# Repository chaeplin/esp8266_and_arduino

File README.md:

* ESP8266 mqtt node

#### Server ####
- mqtt broker : mosquitto
- db : influxdb
- web : grafana, node-red
- collect : mqtt2graphite
- alert : mqttwarn
- control : slack + rtmbot
- define MQTT_MAX_PACKET_SIZE 350

### IDE ###
- CURRENT : Arduino 1.6.8 with git version of https://github.com/esp8266/Arduino

### Library ###
- https://github.com/knolleary/pubsubclient
- https://github.com/milesburton/Arduino-Temperature-Control-Library
- https://github.com/chaeplin/PietteTech_DHT-8266
- https://github.com/bogde/HX711
- https://github.com/Makuna/Rtc
- LiquidCrystal_I2C.h
- https://github.com/openenergymonitor/EmonLib
- https://github.com/bblanchon/ArduinoJson
- https://github.com/MajenkoLibraries/Average
- https://github.com/Yveaux/arduino_vcc
- https://github.com/PaulStoffregen/Time
- https://github.com/z3t0/Arduino-IRremote
- https://github.com/JChristensen/Timer

| name | esp | arduino | desc |
|------|-----|---------|------|
| _01-door-alarm | esp-12 | pro mini | alarm door status using mqtt. first one to learn esp, didn't know how to wake up esp using external intterupt. replaced with _06-power_meter. check _15-esp8266-dash-deepsleep-reset and _48-door-alarm-deepsleep for latest | 
| _02-mqtt-sw-temperature | esp-12 | | control lamp, pub temp, pub radio data. nrf24l01P |
| _03-hx711-scale | esp-12 | pro mini | pub measured weight of pet. hx711, 4 * body scale load cell |
| _04-lcd-dust | esp-01 | nano | display mqtt msg, pub temp/hum, dust, control ir |
| _05-two-ds18b20 | esp-12 | | pub temp. ds18b20. to check deepsleep and life of 2 * AA battery |
| _06-power_meter | esp-12 | | pub power usage, door status. using CT sensor and ADC ---> replaced by _49-emontxv2-esp-01-i2c|
| _07-ac-ir-remote-timer | | pro mini | |
| _08_hc-sr04 | | | hc-sr04 test |
| _09_ir_tx_rx | | nano | to control tv using ir |
| _10-syslog | esp | | udp/syslog example |
| _11-mqtt-lwt-test | esp | | mqtt lwy test |
| _12-wifiscan | esp | | wifi scan test |
| _13-mfrc522-esp8266 | esp | | rfid mfrc522 test |
| _14-mqtt-reconnect-with-reset | esp | | |
| _15-esp8266-dash-deepsleep-reset | esp | | to coltrol lamp. dash like button |
| _16-mqtt-pub-100ms-50ms | esp | | pub test |
| _17-two-esp-one-pub-50ms-one-sub-pub-50ms | esp | | pub test |
| _18-adc-test-using-sdk-1.5| esp | | adc test |
| _19-wifi-test-using-sdk-1.5| esp | | wifi test |
| _20-esp8266-dash-deepsleep-test | esp | | test of _15-esp8266-dash-deepsleep-reset |
| _21-sntp | esp | | sntp test |
| _22-CheckFlashConfig | esp | | CheckFlashConfig |
| _23-attiny85-ir | | tiny85 | ir tx test |
| _24-attiny85-wdt-sleep | | tiny85 | sleep test |
| _25-attiny85-nrf24-ds18b20 | | tiny85 | temp sensor |
| _26-attiny85-nrf24-pin-change-int | | tiny85 | pc int test |
| _27-attiny85-two-85-boost | | tiny85 | distance test |
| _28-attiny85-nrf24-3pin-ir | | tiny85 | distance using ir. checking toilet paper roll |
| _29-attiny85-nrf24-5pin-pin-change-int | | tiny85 | check door bell |
| _30-attiny85-nrf24-5pin-pin-change-int | | tiny85 | check door bell. last one |
| _31-esp-12-gps-ntpd | esp | | gps + ntpd test |
| _32-esp-12-BasicOTA | esp | | ota test |
| _33-esp-12-WiFiClientSecure-mqtt-ssl | esp | | mqtt tlsv1.1 with ip |
| _34-esp-12-WiFiClientSecure-mqtt-ssl-using-dns | esp | | mqtt tlsv1.1 with name |
| _35-esp-12-wpa2-enterprise | esp | | wpa2-enterprise  |
| _36-esp-rtc-mem-test | esp | | rtc mem test |
| _37-wifi-off-modem-sleep | esp | | modem off test |
| _38-wifi-off-light-sleep | esp | | light sleep test |
| _39_esp12-random-test | esp | | random number gen |
| _40_esp12-random-test-udp-report | esp | | random number gen |
| _41-promini-nrf24-ads1115 | | pro mini | i2c adc ads1115 |
| _42-promini-nrf24-32byte | | pro mini | nrf24 32byte test|
| _43-PietteTech_DHT-8266 | esp | | interrup driven dht22 test |
| _44-esp-atmega328p-spi | esp | atmega328p | spi multi byte test |
| _45-esp-atmega328p-i2c | esp | atmega328p | i2c multi byte test |
| _46-esp-atmega328p-spi-i2c | esp | atmega328p | spi and i2c multi byte test |
| _47-esp-dht22-2AA-deepsleep-test | esp | | dht22 test |
| _48-door-alarm-deepsleep | esp | | | door alarm using reed switch |
| _49-emontxv2-esp-01-i2c | esp-01 | atmega328p | emontx v2 plus esp-01 and ds1307. test | 
| _50-promini-nrf24-getntp | | pro mini | nrf24 ntp test |
| _51-attiny85-nrf24-lcd-getntp | | tiny85 | tiny85 spi and i2c mixing |
| _52-attiny85-hx711-nrf24-deprecated | | tiny85 | nrf24 / hx711 / gy-521 test, flash is small |
| _53-esp-01-i2c-lcd | esp-01 | | i2c lcd test |
| _54-atmega328p-nrf24-gy-521-hx711 | | atmega328p | second version of sacle for pet |
| _55-tiny85-dtr-control-esp8266 | | tiny85 | auto reset on Xbee programmer |
| _56-gopro-control | esp-01 | | 4M flash version, to upload gopro picture to twitter |
| _57-tiny85-cds-pir | | tiny85 | to turn off light which has touch sensor |
| _58-esp8266-tyny85-dash-button | esp-01 | tiny85 | second version of dash button |
| _59-esp8266-tyny85-i2c8x8-dash-button | esp-01 | tiny85 | 3rd version of dash button |
| _60-tiny85-pin-int | |tiny85 | PinChangeInterrupt lib test |
| _61-mma-8452-promini | | pro mini | mma-8452 test | 

#### _02-mqtt-sw ####
- esp-12 + nrf24l01p
- power(5v + 3.3V), fuse(10A + 73°C thermal), 1CH relay, SW(top + lamp), PIR, DS18B20(out)
- on/off lamp using mqtt, pub temp outside/pir

#### _03-hx711-scale ####
- esp-12 +(i2c) pro mini
- hx711, load cell, tilt sw
- pub measured weight of pet

#### _04-mqtt-lcd-dust-sensor ####
- esp-01 +(i2c) nano
- lcd(i2c), rtc(i2c), level convertor, Sharp dust sensor, IR sned/recv, dht22
- display clock, temp/humidity(mqtt sub), dust
- control LG_AC using Apple remote

#### _06-power-meter ####
- esp-12
- CT sensor, line tracker
- pub power usage

### _15-esp8266-dash-deepsleep-reset ###
- esp-12
- dash like button
- to control lamp sw

#### _29-attiny85-nrf24-5pin-pin-change-int / _30-attiny85-nrf24-5pin-pin-change-int ####
- attiny 85 + nrf24l01p
- optical isolator
- for door bell
- _30-attiny85-nrf24-5pin-pin-change-int is last one using gammon's wdt

#### _25-attiny85-nrf24-ds18b20 ####
- attiny 85 + nrf24l01p
- two ds18b20
- to check temp

#### _28-attiny85-nrf24-3pin-ir ####
- attiny 85 + nrf24l01p
- ir send and receiver
- to check roll

#### _41-promini-nrf24-ads1115 ###
- pro mini(3.3V) + nrf24l01p + µCurrent GOLD
- to report current measure

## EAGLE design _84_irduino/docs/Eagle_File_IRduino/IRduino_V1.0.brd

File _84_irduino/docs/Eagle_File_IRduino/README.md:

# Eagle_File_IRduino
Eagle file for IRduino

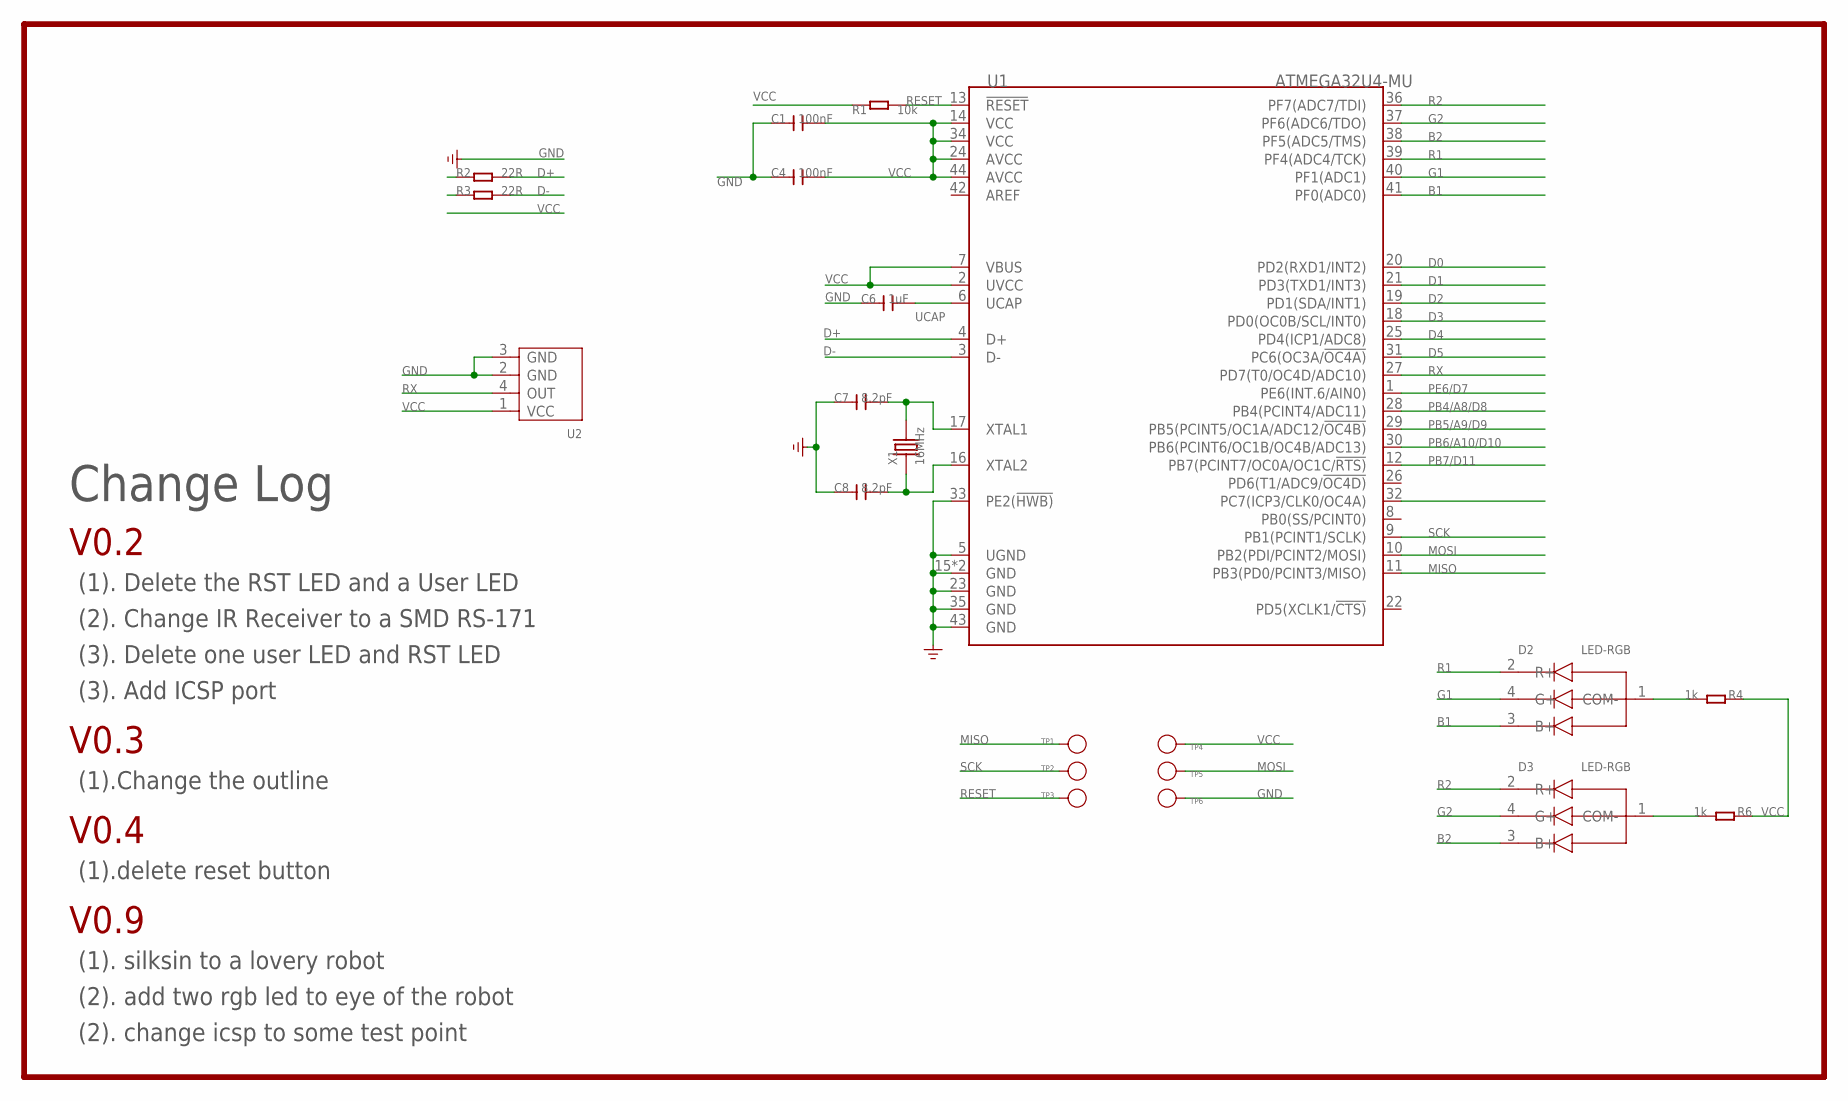
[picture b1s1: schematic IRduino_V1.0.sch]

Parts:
C1, C4: 100nF; C0603
C6: 1uF; C0603
C7, C8: 8.2pF; C0603
D2, D3: LED-RGB; 4P-SMD-1.6X1.5
R1: 10k; R0603
R2, R3: 22R; R0603
R4, R6: 1k; R0603
TP1, TP2, TP3, TP4, TP5, TP6: PAD-TEST-POINT'3535'; TP_3535
U1: ATMEGA32U4-MU; QFN44
U2: RS-171; 4P-SMD-L7.6*W5.75MM
X1: 16MHz; 2P-SMD-5X3.2

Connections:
B1: D2.3 (B+), U1.41 (PF0(ADC0))
B2: D3.3 (B+), U1.38 (PF5(ADC5/TMS))
D0: U1.20 (PD2(RXD1/INT2))
D1: U1.21 (PD3(TXD1/INT3))
D2: U1.19 (PD1(SDA/INT1))
D3: U1.18 (PD0(OC0B/SCL/INT0))
D4: U1.25 (PD4(ICP1/ADC8))
D5: U1.31 (PC6(OC3A/!OC4A))
D+: R2.2, U1.4 (D+)
D++: R2.1
D-: R3.2, U1.3 (D-)
D--: R3.1
G1: D2.4 (G+), U1.40 (PF1(ADC1))
G2: D3.4 (G+), U1.37 (PF6(ADC6/TDO))
GND: C1.1, C4.1, C6.1, C7.1, C8.1, TP6.T, U1.5 (UGND), U1.15 (GND), U1.23 (GND), U1.33 (PE2(!HWB)), U1.35 (GND), U1.43 (GND), U1.TAB (GND), U2.2 (GND), U2.3 (GND)
MISO: TP1.T, U1.11 (PB3(PD0/PCINT3/MISO))
MOSI: TP5.T, U1.10 (PB2(PDI/PCINT2/MOSI))
unnamed: D2.1 (COM-), R4.2
unnamed: D3.1 (COM-), R6.2
unnamed: C7.2, U1.17 (XTAL1), X1.2
unnamed: C8.2, U1.16 (XTAL2), X1.1
PB4/A8/D8: U1.28 (PB4(PCINT4/ADC11))
PB5/A9/D9: U1.29 (PB5(PCINT5/OC1A/ADC12/!OC4B))
PB6/A10/D10: U1.30 (PB6(PCINT6/OC1B/OC4B/ADC13))
PB7/D11: U1.12 (PB7(PCINT7/OC0A/OC1C/!RTS))
PE6/D7: U1.1 (PE6(INT.6/AIN0))
R1: D2.2 (R+), U1.39 (PF4(ADC4/TCK))
R2: D3.2 (R+), U1.36 (PF7(ADC7/TDI))
RESET: R1.2, TP3.T, U1.13 (!RESET)
RX: U1.27 (PD7(T0/OC4D/ADC10)), U2.4 (OUT)
SCK: TP2.T, U1.9 (PB1(PCINT1/SCLK))
UCAP: C6.2, U1.6 (UCAP)
VCC: C1.2, C4.2, R1.1, R4.1, R6.1, TP4.T, U1.2 (UVCC), U1.7 (VBUS), U1.14 (VCC), U1.24 (AVCC), U1.34 (VCC), U1.44 (AVCC), U2.1 (VCC)

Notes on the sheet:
Change Log
(1). Delete the RST LED and a User LED
(2). Change IR Receiver to a SMD RS-171
(3). Delete one user LED and RST LED
V0.2
V0.3
(3). Add ICSP port
(1).Change the outline
V0.4
(1).delete reset button
V0.9
(1). silksin to a lovery robot
(2). add two rgb led to eye of the robot
(2). change icsp to some test point

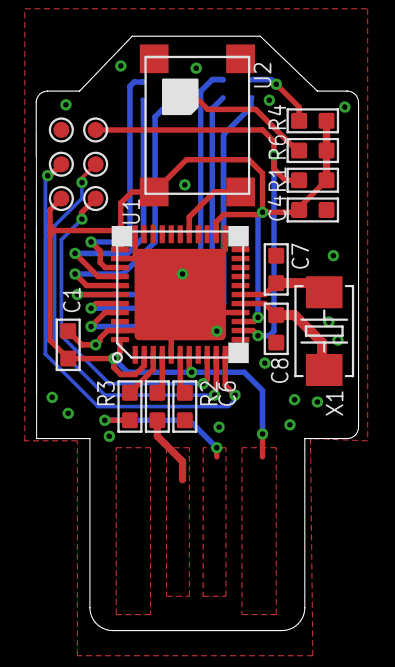
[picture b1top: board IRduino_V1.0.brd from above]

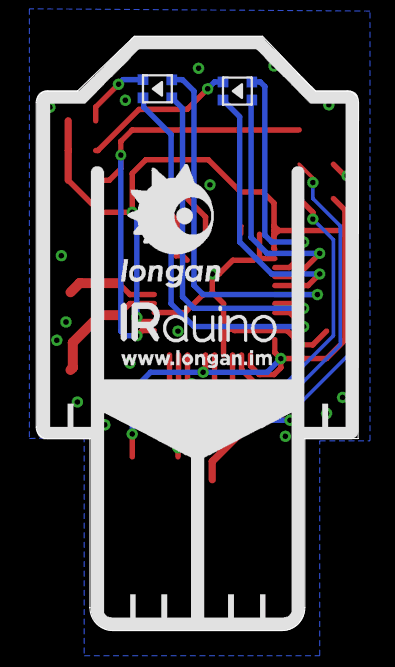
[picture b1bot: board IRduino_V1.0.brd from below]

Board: 2 copper layers, 17.9 x 33.0 mm, 21 parts (2 on the bottom side), 20 nets.

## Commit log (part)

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2016-01-10 calibration
2016-01-10 calibrated
2016-01-10 two ds18b20
2016-01-12 wifi from 1.54 sec to 210ms
2016-01-13 to find cause of reset
2016-01-16 changing cpu to 160MHz over OTA
    no more reset(2day now)
2016-01-17 checking pulse counter of power
2016-01-18 verify fingerprint using host name
2016-01-18 certificate verify
2016-01-19 WPA2-ENTERPRISE
2016-01-20 FreeHeap
2016-01-21 remove noise in pulse counting
2016-01-21 rf24 to rf24 PA/LNA version
2016-01-21 ap_setting.h change, pic add
2016-01-21 reduce wifi connect time to 150 ~ 220ms
2016-01-21 wifi 1.1sec to 152ms
2016-01-23 adjusting report, crt for mqtt client
2016-01-23 remove mqtt cert
2016-01-23 Revert "remove mqtt cert"
    This reverts commit b0061a696f73f3985e871476636015dbbec1f3fe.
2016-01-23 Revert "Revert "remove mqtt cert""
    This reverts commit 7b608709c7d80b3ee336f10499d51f25ff61dc48.
2016-01-25 static ip
2016-01-26 MODEM_SLEEP
2016-01-26 wifi_fpm_set_wakeup_cb : not work
2016-01-28 tx power and rate limit
2016-01-28 msg to influxdb udp
2016-01-28 logging to multiple server
2016-01-29 ads1115 test
2016-01-29 delay change
2016-01-30 attachInterrupt and udp test
2016-01-30 PinChangeInterrupt
2016-01-30 add radio channel and sendUdpmsg
2016-01-30 remove PinChangeInterrupt
2016-01-30 nrf24 multi ch and current test
2016-01-30 move radio power up/down
2016-01-30 250 reports / sec
2016-01-31 simple logic / 300 recore / sec
2016-01-31 // for PubSubClient 2.5 #define MQTT_MAX_PACKET_SIZE 250 //#define MQTT_KEEPALIVE 60
2016-01-31 Revert "// for PubSubClient 2.5 #define MQTT_MAX_PACKET_SIZE 250 //#define MQTT_KEEPALIVE 60"
    This reverts commit 972c98eee3b66ee306079ec87a9a2a6522ddc7a8.
2016-01-31 using rtc mem to preserve rev count
2016-02-01 to debug more
2016-02-02 unit to nA
2016-02-02 report light status when booting
2016-02-02 report interval 1 min to 1 sec
2016-02-02 RF24_PA_LOW to RF24_PA_MIN
2016-02-03 1 sec to 10 sec
2016-02-03 radio.enableDynamicPayloads test
2016-02-04 update ampere meter
2016-02-04 radio change
    radio.enableDynamicPayloads,
    radio.setDataRate(RF24_1MBPS),
    radio.setRetries(5, 15),
    break to return,
    preserve light status after reset/update
2016-02-05 data size
2016-02-05 radio.setDataRate(RF24_1MBPS), radio.enableDynamicPayloads
2016-02-09 test PietteTech_DHT
2016-02-09 test
2016-02-09 test 2
2016-02-09 test 3
2016-02-09 radio_test_result
    with setWaitForConversion and PietteTech_DHT-8266
    —> check bool RF24::write
2016-02-10 PietteTech_DHT test
2016-02-10 DHT.acquireAndWait(0)
2016-02-10 _edges debug
2016-02-10 dht edges report
2016-02-10 PietteTech_DHT-8266 timing test with DHT_DEBUG_TIMING on/off
2016-02-11 DHT_DEBUG_TIMING off
2016-02-11 timing
2016-02-11 DHT_DEBUG_TIMING
2016-02-11 DHTLIB_ONE_TIMING
    108 to 109
2016-02-11 DHTLIB_ONE_TIMING, calcIrms, button,
2016-02-12 DHT.getStatus, power meter
2016-02-12 DHT_SAMPLE_INTERVAL
2016-02-13 _sensor_report_count
2016-02-13 remoce locked up and reset of lcd
2016-02-13 swap flash from 512K to 4M
    ./esptool.py -p /dev/cu.usbserial-A703X38A erase_flash
    ./esptool -vv -cd ck -cb 115200 -cp /dev/cu.usbserial-A703X38A -ca
    0x3FC000 -cf ./esp_init_data_default1.5.2.bin
2016-02-13 json update
2016-02-14 lcd update
2016-02-14 ADS1115 + µCurrent GOLD, DHT timeout
2016-02-15 report Cpu Freq
2016-02-15 move up radio
2016-02-17 radio temp, lcd dust, swtemp
    1) swtemp : remove dht22(too many err with this unit, move to lcd dust)
    2) lcd dust : change temp subs topic
    3) radio temp : 10 sec to 60 sec
2016-02-17 add DHT22
2016-02-17 sw-temp : rf24 with irq
2016-02-17 syslog update
2016-02-17 DEBUG_PRINT and RTC
2016-02-17 readme
    rtc add, dht22 moved
2016-02-18 lcd.init
2016-02-18 report 3s to 5s, radio rx option
2016-02-19 debug on
2016-02-19 rtc test is done
    remove rtc
2016-02-19 dust : rtc test again, sw-temp : to 160MHz
2016-02-20 ICACHE_RAM_ATTR test
2016-02-24 nrf24 : with irq : 280, no irq 380
2016-02-26 dht22 110 to 104
2016-02-26 spi test
2016-02-27 i2c test
2016-02-27 i2c twi_setClock
2016-02-27 dht 104 to 110
2016-02-28 Read me
2016-02-28 add source
2016-02-28 i2c result
2016-02-29 move folder
2016-02-29 spi-i2c-test
2016-03-01 drop irq with nrf24l01, add dht22 again
2016-03-01 ds18b20 is nan
2016-03-02 display update
2016-03-03 pin definition
2016-03-03 dht22 deepsleep test
2016-03-04 dht2 remove and deepsleep test
2016-03-05 pic link update
2016-03-05 reset to restart
2016-03-06 button and lcd update
    - button : read me
    - lcd : host count
2016-03-07 blog for button
2016-03-08 lcd, light sleep, dht22
    lcd : report to 5 sec
    light sleep : wake up with gpio event
    dht22 : ladyada’s version test
2016-03-08 light_sleep_current
2016-03-08 scale, light sleep, dht22
    scale : add icmp test
    light sleep : time test
    dht22 : more test
2016-03-09 scale, dht
    scale : icmp
    dht : deepsleep test
2016-03-10 hx711, lcd, button, dht
    hx711 : core to 2.1.0
    lcd /nano : rgb test
    button : more oneshot circuit
    dht : sampling interval
2016-03-12 door alarm
2016-03-12 debug using udp
2016-03-12 current
2016-03-13 power control with GPIO 0
2016-03-14 more test on dht22
2016-03-14 pins
2016-03-14 test : i2c to ds1307, put low SDA
2016-03-16 emontxv2 and hx711
    hx711 : remove detachInterrupt
    emontxv2 : i2c test setup
2016-03-16 esp-01 test setup
2016-03-16 pics
2016-03-16 use interrupt between masters
2016-03-16 add 4.7k pullup to D6 to TX
2016-03-17 adding ct, pulse, and door
2016-03-17 current only test
2016-03-18 for calibration
2016-03-18 add door alarm
2016-03-18 report ct data
2016-03-18 dht22 with pullup
2016-03-19 CHANGE PIN EDGE
2016-03-19 in calibration
2016-03-19 report
2016-03-21 using reed, pics
2016-03-22 report roll status change
2016-03-22 pics update
2016-03-22 pics 2
2016-03-24 hx711, oics
2016-03-25 hx711 cell Schematic
2016-03-26 ackpayload test
2016-03-27 radio.writeAckPayload
2016-03-27 time_ackpayload and time_rxpayload
2016-03-27 Alarm.alarmRepeat
2016-03-28 get time using AckPayload
2016-03-28 debug
2016-03-28 3 ack payload
2016-03-30 send data to nrf using ack payload
2016-03-31 remove TimeAlarms.h which needs delay in loop
2016-04-01 timer
2016-04-01 timer update
2016-04-04 attiny85 with gy-521 test
2016-04-04 sw, gy-521
    sw : time_reqpayload for ch 4
    gy-521 : more test
2016-04-06 misc
2016-04-07 flash change
2016-04-07 will use atmega328p
2016-04-07 atmega328 test
2016-04-07 remove solar sata
2016-04-08 time payload for roll detector
2016-04-10 solar lcd and hx711
    solar lcd : adding customChar
    hx711 : sleep done. todo : get hx711 value and report
2016-04-11 hx711
2016-04-11 scale and report
2016-04-12 dtr control : auto flash mode and reset
2016-04-12 scale without gy-521
2016-04-12 bug in tare
    need to check
2016-04-13 adding tare
2016-04-14 tare at every 2 hour
2016-04-14 gopro control test
2016-04-15 hmac_sha1 test
2016-04-15 icon update
2016-04-15 rtc_check
    https://github.com/chaeplin/esp8266_and_arduino/issues/27
2016-04-15 new scale
2016-04-16 adding rtc and time ack payload
    https://github.com/chaeplin/esp8266_and_arduino/issues/30
2016-04-17 post test
2016-04-17 bugs in keys
2016-04-24 switch, esp reset control, twitter post
    02: mqtt sw - update mqtt when button is pressed and alarm is on
    55 : change timing
    56 : image simple post is done
2016-04-24 httptospiffs test
2016-04-24 phase 3 test
2016-04-24 go pro image download and tweet
2016-04-26 adding ds3231
2016-04-27 add progress
2016-04-28 add speed
2016-04-28 speed and file name change
2016-04-29 without ds3231
    change file name
2016-04-29 reset not work with micropython
2016-04-29 config on spiffs
2016-04-29 stream->setTimeout(50);
2016-04-30 rtc test
2016-04-30 config on rtc
2016-04-30 print count
2016-05-03 add up/down error checking
2016-05-04 default to spiffs format, 5MP
2016-05-06 new button
2016-05-06 image resize
2016-05-07 Revert "ces test"
    This reverts commit 361e18adafb3d1fe0d31cb5207f73a10f86c4456.
2016-05-07 ReadMe update
2016-05-07 resize image
2016-05-07 resize
2016-05-07 ReadMe
2016-05-08 add test
2016-05-13 mtu 1460 to 1400
    too many upload errs.
2016-05-13 28KB
2016-05-15 112KB
2016-05-16 download count 1700 to 1800
2016-05-18 PinChangeInterrupt / attiny85
2016-05-18 button with matrix
2016-05-20 read sd card
2016-05-20 typo in readme
2016-05-21 disable gopro mode / DS3231SquareWavePin_ModeNone
2016-05-21 sd test
2016-05-22 sharing sd card of gopro fail
2016-05-23 adding 8x8 heart
2016-05-26 add auto shutdown off
2016-05-29 wifi error report
2016-05-30 IR TEST
2016-05-30 asString on processing_info
2016-06-02 tweet test
2016-06-02 twitter test
2016-06-04 mma8452 test
2016-06-04 button test
2016-06-05 long and short button press
2016-06-05 clock 160M, twi 200K test
2016-06-05 remove twi_setClock(200000)
2016-06-05 rtc_boot_mode.gopro_mode
    https://github.com/chaeplin/esp8266_and_arduino/issues/34
2016-06-07 debug on ph 6
2016-06-07 thing+
2016-06-07 160MHz and go pro PH 6 debug
2016-06-10 add off timer to switch
2016-06-14 lcddust to i2c
2016-06-15 go pro external signal and auto exec to turn on/off wifi
2016-06-15 esp01 to esp12
2016-06-16 dust : compare result. gopro : change gopro on time
2016-06-16 adding powerAC
2016-06-16 adding ir for ac
2016-06-16 button optimize
2016-06-16 gopro : bug in ph 0. add checking cmd
2016-06-17 status report
2016-06-17 report sub change
2016-06-18 indent of { and display on change
2016-06-18 check ac on/off using powerAC
2016-06-20 reset esp on bbutton_downp_isr
2016-06-20 remove while.
2016-06-20 nodemcu pins
2016-06-23 static ip setup before wifi begin
2016-06-23 go pro control.
2016-06-23 sometimes status jumping to timed out, need to check
2016-06-23 adding ds18b20
2016-06-24 TSOP382 pin
2016-06-25 slackbot test
2016-06-26 ir receive and timer mode
2016-06-26 send timer mode when checking
2016-06-26 slack ir bot for lgWhisen
2016-06-26 report ir status
2016-06-26 AC_CONF_
2016-06-26 change timer
2016-06-26 irrecv.disableIRIn
2016-06-27 add current temp
2016-06-27 snedcheck when mode changed
2016-06-27 ac control update.
    1) ignore retained ac control. always start with ac off
    2) sendCheck when mode changed
    3) add irrecv.enableIRIn(); to nano
2016-06-27 timer mode change
2016-06-29 esp(i2c m) + mega328p(i2c m +s)
2016-06-30 ac temp and flow set
2016-06-30 led status
2016-07-01 remove delay
2016-07-02 WiFiManager test
2016-07-02 Ticker.h
2016-07-03 disable DEBUG_PRINT to test dht22
2016-07-08 disable gopro
2016-07-12 webSocket_config
2016-07-14 change lcd byte
2016-07-14 ac-ir-for-bedroom
2016-07-15 remove dup report
2016-07-15 remove dup msg and delay in report && pir test
2016-07-18 do not send data to nano when mode is off
2016-07-20 add ota
2016-07-20 add ArduinoOTA.handle();
2016-07-20 add makefile
2016-07-20 subscribe to 6
2016-07-20 bignoreACretained = false
2016-07-21 ota nad cou hz with makefile
2016-07-22 mqtt node for HAP-NodeJS
2016-07-23 ArduinoOTA.handle();
2016-07-23 button debounce with pull up and RISING
2016-07-23 WiFi.hostname
2016-07-23 button bounce
2016-07-24 subscribe a topic and uodate state
2016-07-24 publish sw state every 5sec
2016-07-24 ignore mqtt msg BETWEEN_RELAY_ACTIVE time
2016-07-24 compare AC mode
2016-07-25 SI7021 test
2016-07-27 nest bridge test
2016-07-27 d1 mini
2016-07-28 lgWhisen.alrclean_on
2016-07-29 remove airclean
2016-07-29 report temperature and humidity / mqtt to tls
2016-07-29 swtemp to tls
2016-07-31 remove Serial.println
2016-08-02 check mqtt reconnect
2016-08-02 remove serial.print
2016-08-02 ticker.attach(1, tick);
2016-08-03 tx power
2016-08-04 on/off ac using nest bridge
2016-08-04 indent
2016-08-05 send initial state
2016-08-06 homekit-accessories
2016-08-07 temp set by msg
2016-08-07 control by homekit
2016-08-07 5 min pir
2016-08-07 presence
2016-08-07 mqtt to tls
2016-08-07 send reset reson
2016-08-14 debug ac mode change
2016-08-14 Update to git version
2016-08-14 validate callback input and compare to current value
2016-08-28 display more date
2016-09-09 QR test
2016-09-19 oled qrcode and nfc with pn532
2016-10-07 nfc with dash
2016-10-07 add lib url
2017-04-02 door alarm to slack
2017-07-13 some update
2017-10-15 4*4 led matrix
2017-10-18 rtm.start to rtm.connect
2018-05-21 door + pir
2018-05-21 status update
2018-06-18 add reset
